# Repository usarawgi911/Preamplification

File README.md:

# Preamplification
A Preamplifier circuit intended for biosignals

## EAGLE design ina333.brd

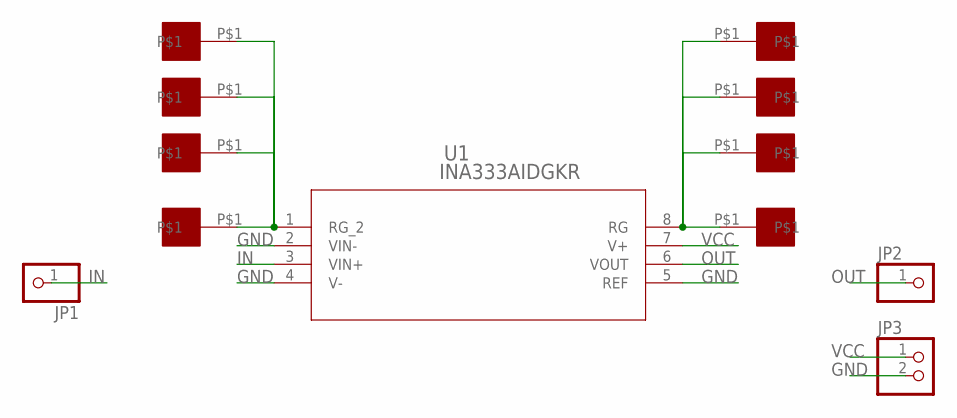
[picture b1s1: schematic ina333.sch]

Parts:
JP1, JP2: PINHD-1X1; 1X01
JP3: PINHD-1X2; 1X02
U1: INA333AIDGKR; DGK8
U$1, U$2, U$3, U$4, U$5, U$6, U$7, U$8: PAD

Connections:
GND: JP3.2, U1.2 (VIN-), U1.4 (V-), U1.5 (REF)
IN: JP1.1, U1.3 (VIN+)
unnamed: U1.1 (RG_2), U$1.P$1, U$3.P$1, U$5.P$1, U$6.P$1
unnamed: U1.8 (RG), U$2.P$1, U$4.P$1, U$7.P$1, U$8.P$1
OUT: JP2.1, U1.6 (VOUT)
VCC: JP3.1, U1.7 (V+)

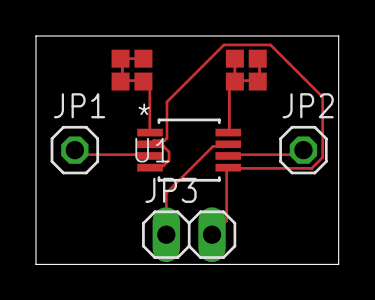
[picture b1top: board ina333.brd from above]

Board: 2 copper layers, 16.8 x 12.7 mm, 12 parts (0 on the bottom side), 6 nets.
